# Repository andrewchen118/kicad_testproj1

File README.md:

# kicad_testproj1
first test project based on ai03's wiki tutorial
> andrew is very pp and forgot README.md
> no i was just too lazy to add one lmao

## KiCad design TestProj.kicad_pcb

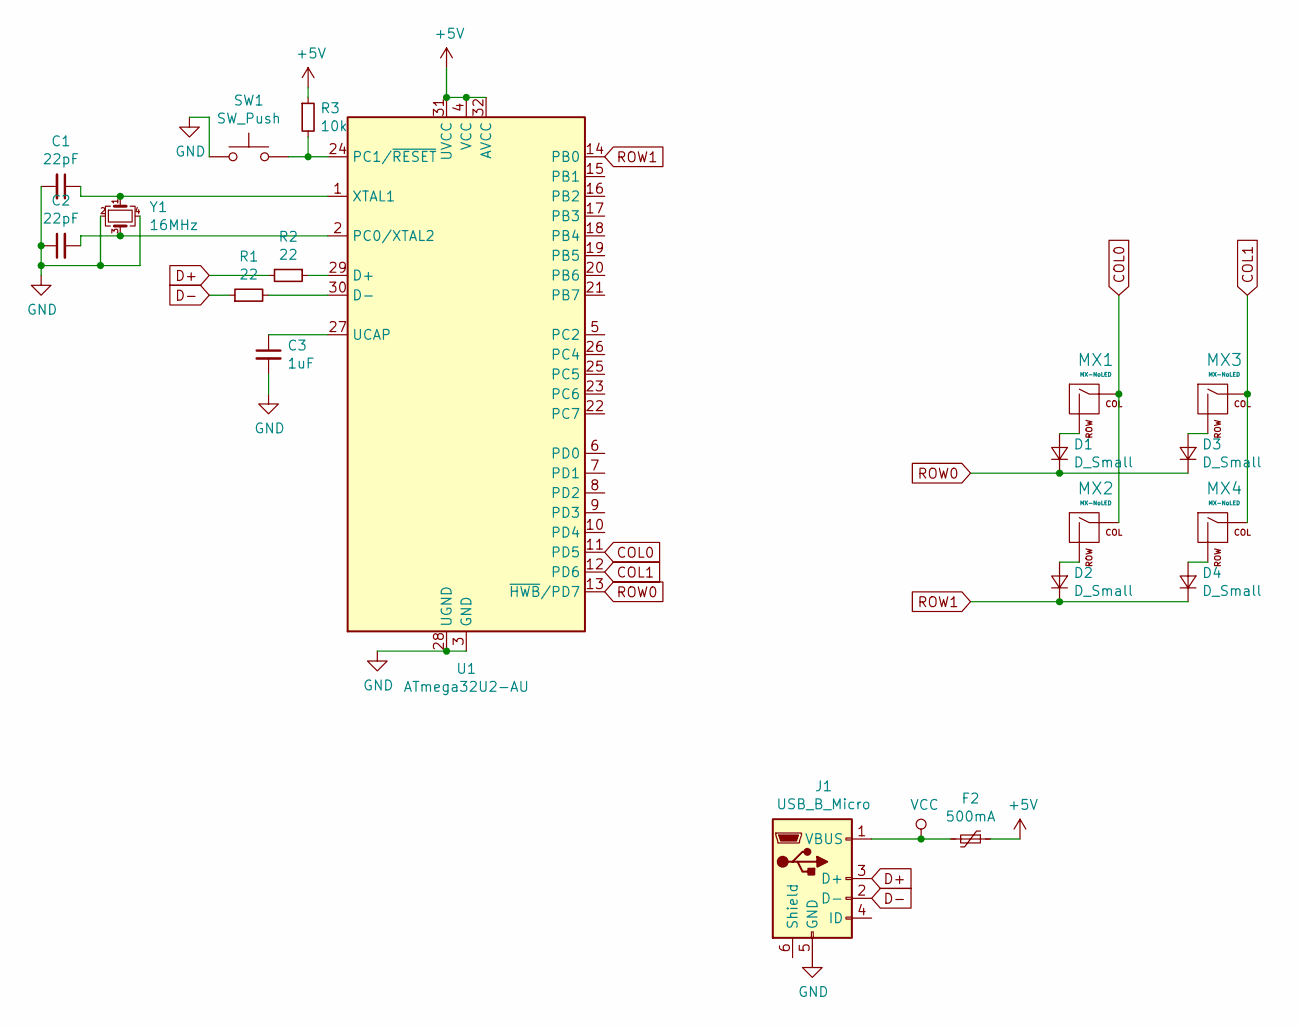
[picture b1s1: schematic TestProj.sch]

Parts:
C1, C2: 22pF; C_0805_2012Metric_Pad1.15x1.40mm_HandSolder
C3: 1uF; C_0805_2012Metric_Pad1.15x1.40mm_HandSolder
D1, D2, D3, D4: D_Small; D_SOD-123
F2: 500mA; Fuse_1206_3216Metric
J1: USB_B_Micro; USB_Micro-B_Amphenol_10103594-0001LF_Horizontal
MX1, MX2, MX3, MX4: MX-NoLED; MXOnly-1U
R1, R2: 22; R_0805_2012Metric_Pad1.15x1.40mm_HandSolder
R3: 10k; R_0805_2012Metric_Pad1.15x1.40mm_HandSolder
SW1: SW_Push; SKQG-1155865
U1: ATmega32U2-AU; TQFP-32_7x7mm_P0.8mm
Y1: 16MHz; Crystal_SMD_3225-4Pin_3.2x2.5mm_HandSoldering

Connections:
+5V: F2.1, R3.1, U1.4 (VCC), U1.31 (UVCC), U1.32 (AVCC)
COL0: MX1.1 (COL), MX2.1 (COL), U1.11 (PD5)
COL1: MX3.1 (COL), MX4.1 (COL), U1.12 (PD6)
D+: J1.3 (D+), R2.2
D-: J1.2 (D-), R1.1
GND: C1.2, C2.1, C3.2, J1.5 (GND), SW1.1, U1.3 (GND), U1.28 (UGND), Y1.2, Y1.4
unnamed: C1.1, U1.1 (XTAL1), Y1.1
unnamed: C2.2, U1.2 (PC0/XTAL2), Y1.3
unnamed: C3.1, U1.27 (UCAP)
unnamed: D1.2 (A), MX1.2 (ROW)
unnamed: D2.2 (A), MX2.2 (ROW)
unnamed: D3.2 (A), MX3.2 (ROW)
unnamed: D4.2 (A), MX4.2 (ROW)
unnamed: R1.2, U1.30 (D-)
unnamed: R2.1, U1.29 (D+)
unnamed: R3.2, SW1.2, U1.24 (PC1/~RESET)
ROW0: D1.1 (K), D3.1 (K), U1.13 (~HWB~/PD7)
ROW1: D2.1 (K), D4.1 (K), U1.14 (PB0)
VCC: F2.2, J1.1 (VBUS)

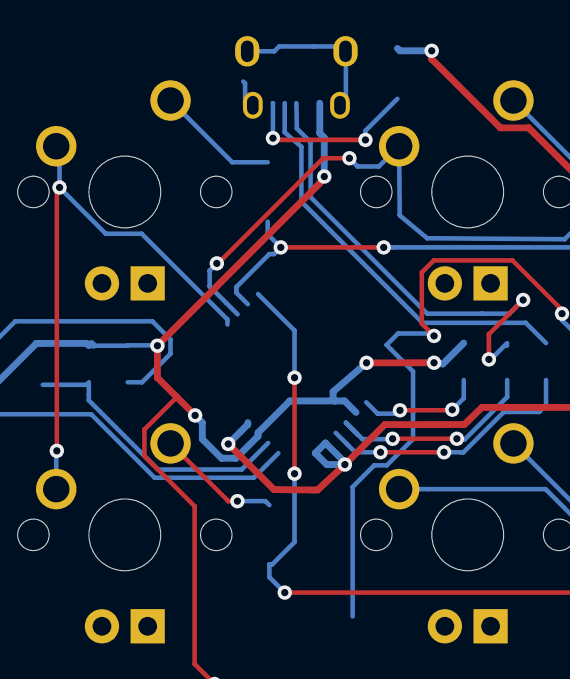
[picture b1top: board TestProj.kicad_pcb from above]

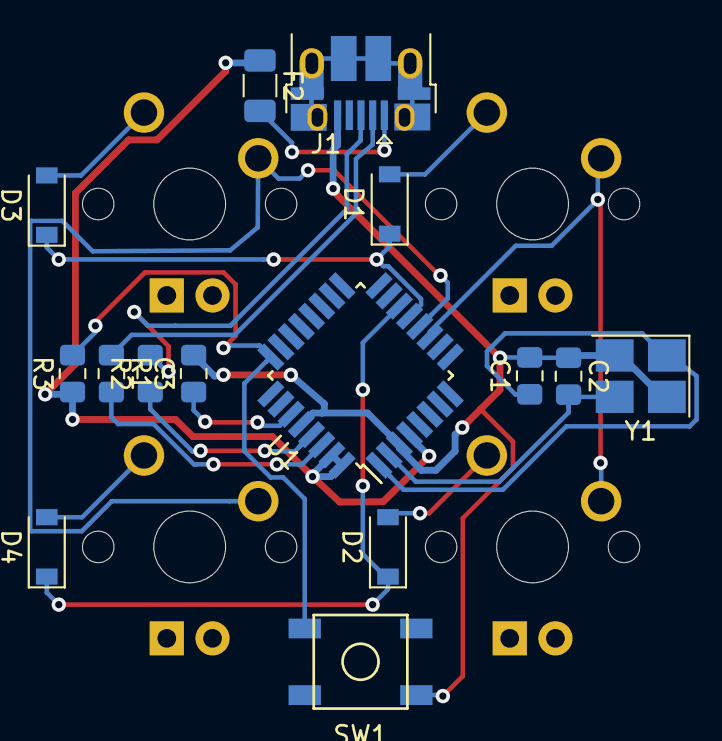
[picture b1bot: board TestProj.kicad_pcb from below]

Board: 2 copper layers, 19 parts (15 on the bottom side), 19 nets.

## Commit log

2019-08-06 add submodules: ai03 footprint libraries
2019-08-06 add symbol and footprint paths
2019-08-06 schematic finished + pcb footprints mapped
2019-08-06 fix dupe switches
2019-08-07 early pcb routing
2019-08-10 starting from scratch with atmega32u2
2019-08-11 a poor routing job 8)
